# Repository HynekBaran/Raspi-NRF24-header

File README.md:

# Raspi-NRF24-header
Raspberry Pi NRF24L01 header (incl. 5V to 3V3 voltage regulator and additional SPI header)

This PCB is modified version of
https://www.openhardware.io/view/17/Raspberry-Pi2-GPIO-interface-for-NRF24L01.

####Usage with MySensors
May be used as MySensors.org gateway, see
https://github.com/mysensors/Raspberry
for details.

#####Installation of MySensor's gateway
``` bash
 # NRF24 Libraries
 apt install git make g++ rsyslog
 git clone "https://github.com/TMRh20/RF24.git"
 cd RF24/
 make all
 cd ..
 # MySensor gateway for Raspberry Pi
 git clone "https://github.com/mysensors/Raspberry.git"
 cd Raspberry/
 make all
 sudo make install
 sudo make enable-gwserial
 ```
 
#####Usage
 
 Make your gateway available as `/dev/ttyMySensorsGateway` by running
 ```bash
 sudo make enable-gwserial
 ```

 If accesing by some software controller, it has to have an access rights to above device.
 E.g., when using FHEM controller, allow it to access /dev/ttyMySensorsGateway by
``` bash
 usermod -a -G tty fhem
 ```
 
####PWR_SEL jumper (must be shorted correctly)
Select power source by connecting a jumper to the proper pair of pins:
```
Short 3V3_NRF <---> 3V3PI  if using Raspberry's internal 3V3 (take care!)
Short 3V3_NRF <---> 3V3EXT if assembled LD117 regulator 
                              and feed the device via EXT_PWR_IN 5V pin (e. g. connected to Raspi 5V)
```
Without a proper short/jumper described above, radio is not powered!

####PWR_OUT1, PWR_OUT2 headers (optional)
PWR_OUT1, PWR_OUT2 headers may be used to feed any optional external 3.3 V device

<a href="https://oshpark.com/shared_projects/ncBBwenI"></img></a>

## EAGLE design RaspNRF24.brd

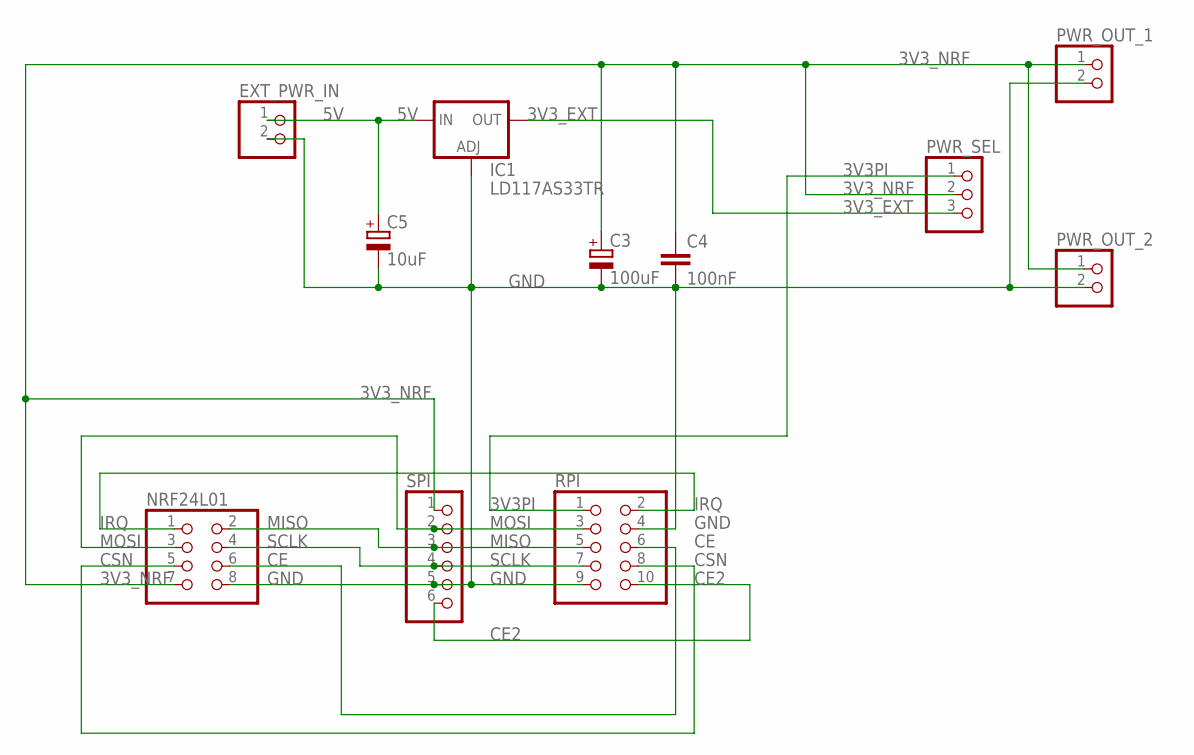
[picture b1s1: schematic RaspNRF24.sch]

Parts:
C3: 100uF; E2,5-5
C4: 100nF; C025-024X044
C5: 10uF; E2-4
EXT_PWR_IN: PINHD-1X2; 1X02
IC1: LD117AS33TR; SOT223
NRF24L01: PINHD-2X4; 2X04
PWR_OUT_1, PWR_OUT_2: PINHD-1X2; 1X02
PWR_SEL: PINHD-1X3; 1X03
RPI: PINHD-2X5; 2X05
SPI: PINHD-1X6; 1X06

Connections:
3V3PI: PWR_SEL.1, RPI.1
3V3_EXT: IC1.4 (OUT), PWR_SEL.3
3V3_NRF: C3.+, C4.1, NRF24L01.7, PWR_OUT_1.1, PWR_OUT_2.1, PWR_SEL.2, SPI.1
5V: C5.+, EXT_PWR_IN.1, IC1.3 (IN)
CE: NRF24L01.6, RPI.6
CE2: RPI.10, SPI.6
CSN: NRF24L01.5, RPI.8
GND: C3.-, C4.2, C5.-, EXT_PWR_IN.2, IC1.1 (ADJ), NRF24L01.8, PWR_OUT_1.2, PWR_OUT_2.2, RPI.4, RPI.9, SPI.5
IRQ: NRF24L01.1, RPI.2
MISO: NRF24L01.2, RPI.5, SPI.3
MOSI: NRF24L01.3, RPI.3, SPI.2
SCLK: NRF24L01.4, RPI.7, SPI.4

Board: 2 copper layers, 12 parts (1 on the bottom side), 12 nets, no tracks yet.

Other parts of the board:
U$1: OSHWLOGO_TOL_0.2

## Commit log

2016-01-26 Ordered on OHSpark.com https://oshpark.com/shared_projects/ncBBwenI
2016-01-26 PDF schema
2016-02-23 Schemas and photos added.
